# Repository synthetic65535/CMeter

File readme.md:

# CMeter
Измеритель тока фрикции.

* Используемый микроконтроллер: atmega8
* Среда разработки: KiCad
* Прошивка для микроконтроллера: [Здесь](https://github.com/synthetic65535/CMeterFirmware)

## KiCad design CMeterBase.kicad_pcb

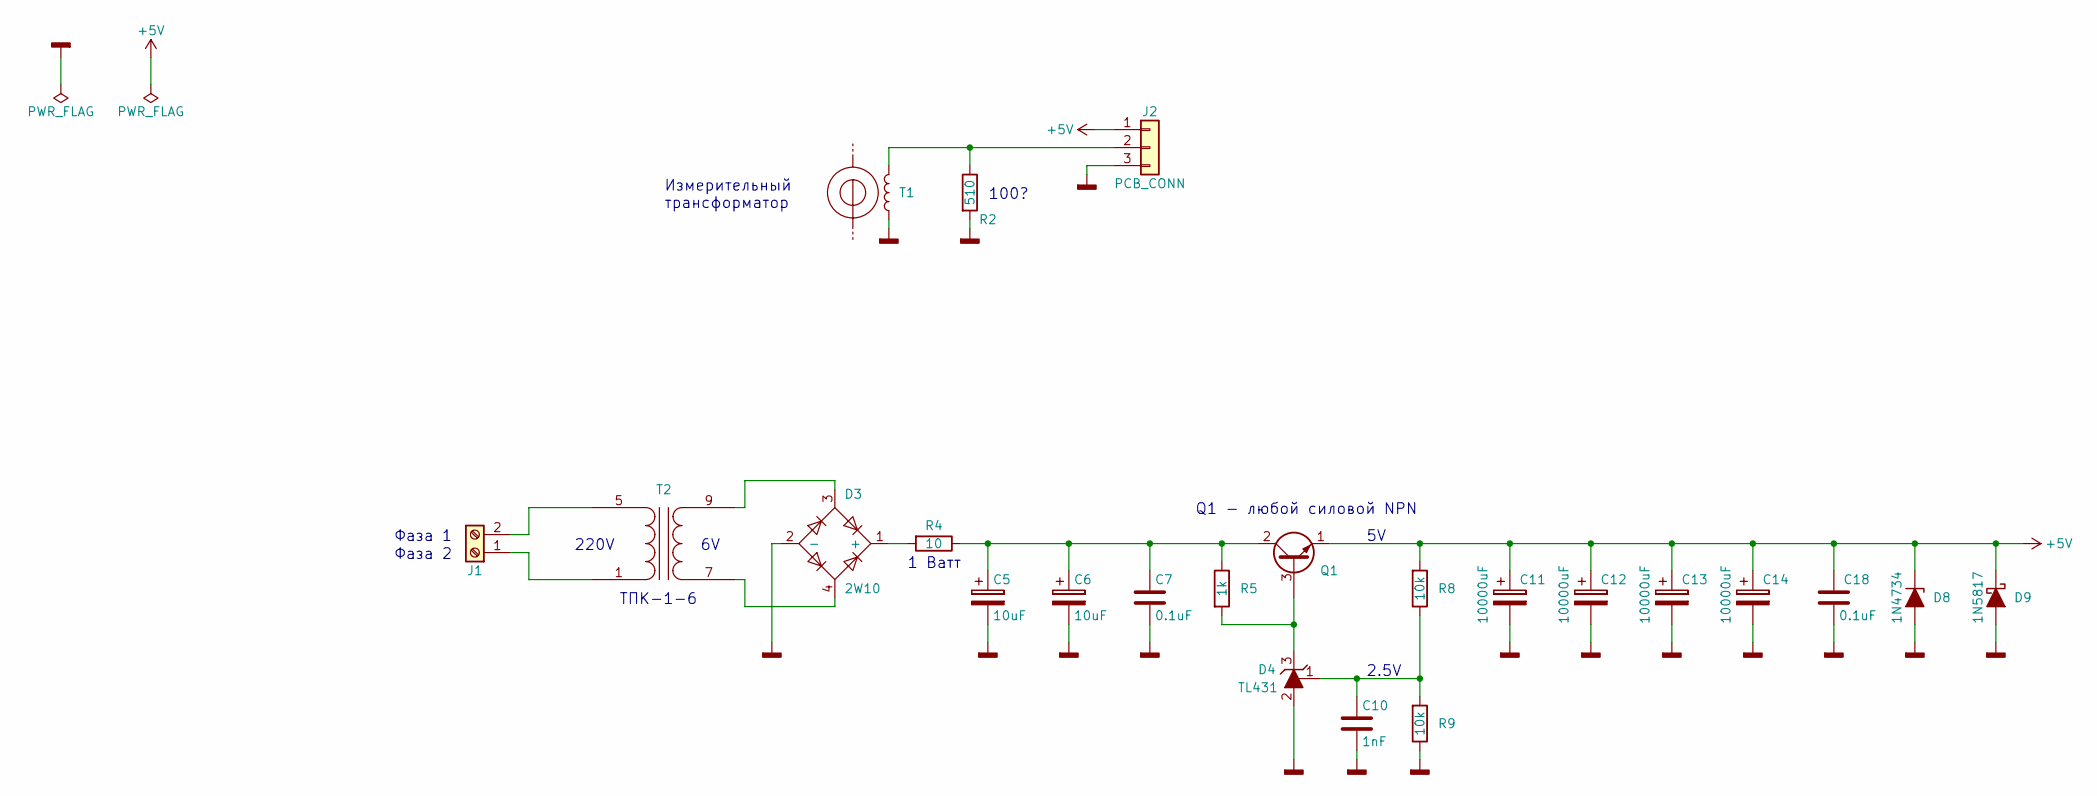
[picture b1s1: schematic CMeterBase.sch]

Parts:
C5, C6: 10uF; CP_Radial_D5.0mm_P2.00mm
C7, C18: 0.1uF; CAP
C10: 1nF; CAP
C11: 10000uF; CAP_D16_L36
C12, C13, C14: 10000uF; CAP_D16_L36-2
D3: 2W10; WOB_Bridge_Rectifier
D4: TL431
D8: 1N4734; DO-41
D9: 1N5817; DO-41
J1: Screw_Terminal_01x02; KLS2-306V-5.00-02P-2S
J2: PCB_CONN; Pin_Header_Straight_1x03_Pitch2.54mm
Q1: Q_NPN_ECB; TO-126_Horizontal
R2: 510; RES
R4: 10; RES1W
R5: 1k; RES
R8, R9: 10k; RES
T1: L_Measure; AC-1005_ZMCT102
T2: TPK-2-6; TPK-1

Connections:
+5V: C11.1, C12.1, C13.1, C14.1, C18.1, D8.1 (K), D9.1 (K), J2.1, Q1.1 (E), R8.2
GNDD: C5.2, C6.2, C7.2, C10.2, C11.2, C12.2, C13.2, C14.2, C18.2, D3.2 (-), D4.2 (A), D8.2 (A), D9.2 (A), J2.3, R2.2, R9.1, T1.1
unnamed: C5.1, C6.1, C7.1, Q1.2 (C), R4.1, R5.1
unnamed: C10.1, D4.1 (REF), R8.1, R9.2
unnamed: D3.1 (+), R4.2
unnamed: D3.3, T2.9 (SA)
unnamed: D3.4, T2.7 (SB)
unnamed: D4.3 (K), Q1.3 (B), R5.2
unnamed: J1.1, T2.1 (AA)
unnamed: J1.2, T2.5 (AB)
unnamed: J2.2, R2.1, T1.2

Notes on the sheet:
Фаза 2
Фаза 1
Измерительный трансформатор
220V
1 Ватт
2.5V
Q1 - любой силовой NPN
100?
ТПК-1-6

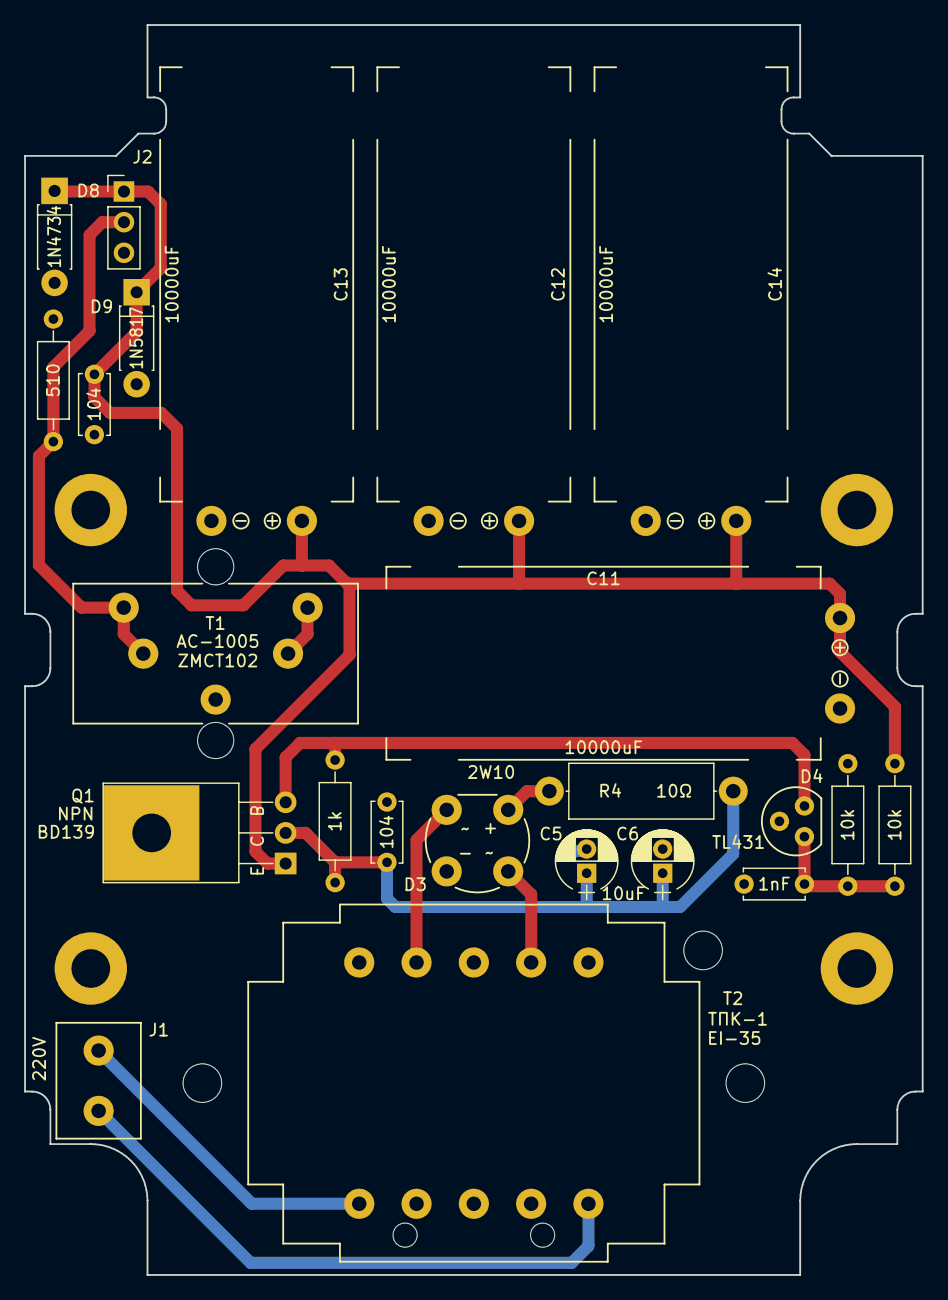
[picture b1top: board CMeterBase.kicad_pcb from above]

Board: 2 copper layers, 74.4 x 103.6 mm, 24 parts (0 on the bottom side), 11 nets.

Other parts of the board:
CASE: Case_G1202_Base; Case_G1202_Base-2

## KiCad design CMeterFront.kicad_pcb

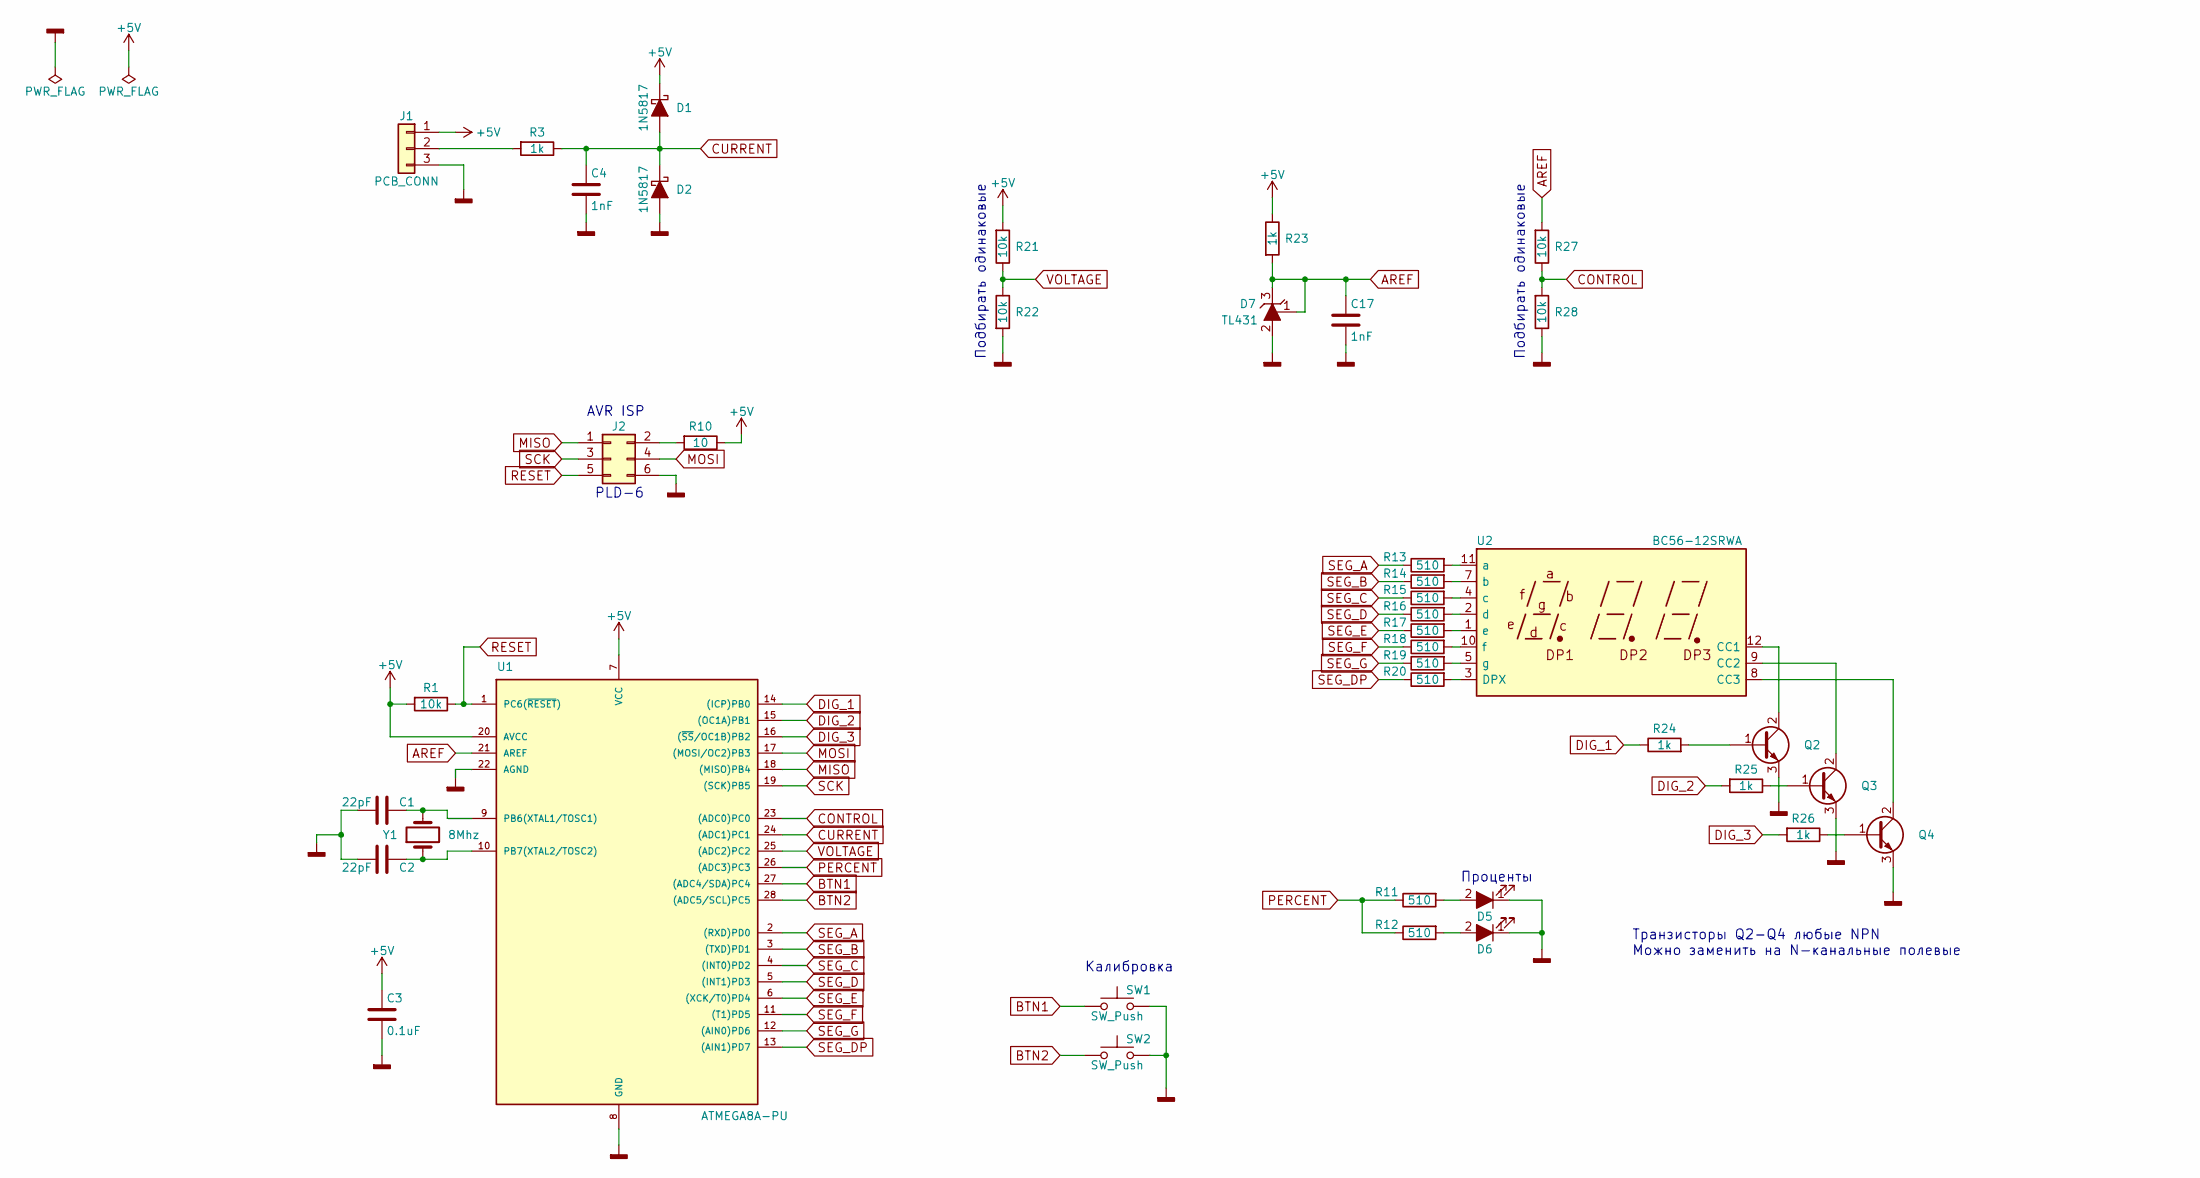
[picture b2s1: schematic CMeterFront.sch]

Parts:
C1, C2: 22pF; CAP
C3: 0.1uF; CAP
C4, C17: 1nF; CAP
D1, D2: 1N5817; DO-41
D5, D6: LED_ALT; LED_D5.0mm
D7: TL431
J1: PCB_CONN; Pin_Header_Straight_1x03_Pitch2.54mm
J2: PLD-6; AVR_ISP
Q2, Q3, Q4: Q_NPN_BCE; Q_BCE
R1, R21, R22, R27, R28: 10k; RES
R3, R23, R24, R25, R26: 1k; RES
R10: 10; RES
R11, R12, R13, R14, R15, R16, R17, R18, R19, R20: 510; RES
SW1, SW2: SW_Push; SW_PUSH_6mm_h5mm
U1: ATMEGA8A-PU; TRS-28_Connfly
U2: BC56-12SRWA; BC56-12SRWA-2
Y1: 8Mhz; Crystal_HC49-4H_Vertical

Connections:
+5V: C3.1, D1.1 (K), J1.1, R1.2, R10.1, R21.2, R23.1, U1.7 (VCC), U1.20 (AVCC)
AREF: C17.1, D7.1 (REF), D7.3 (K), R23.2, R27.2, U1.21 (AREF)
BTN1: SW1.1, U1.27 ((ADC4/SDA)PC4)
BTN2: SW2.1, U1.28 ((ADC5/SCL)PC5)
CONTROL: R27.1, R28.2, U1.23 ((ADC0)PC0)
CURRENT: C4.1, D1.2 (A), D2.1 (K), R3.1, U1.24 ((ADC1)PC1)
DIG_1: R24.1, U1.14 ((ICP)PB0)
DIG_2: R25.2, U1.15 ((OC1A)PB1)
DIG_3: R26.2, U1.16 ((~SS~/OC1B)PB2)
GNDD: C1.2, C2.2, C3.2, C4.2, C17.2, D2.2 (A), D5.1 (K), D6.1 (K), D7.2 (A), J1.3, J2.6, Q2.3 (E), Q3.3 (E), Q4.3 (E), R22.2, R28.1, SW1.2, SW2.2, U1.8 (GND), U1.22 (AGND)
MISO: J2.1, U1.18 ((MISO)PB4)
MOSI: J2.4, U1.17 ((MOSI/OC2)PB3)
unnamed: C1.1, U1.9 (PB6(XTAL1/TOSC1)), Y1.2
unnamed: C2.1, U1.10 (PB7(XTAL2/TOSC2)), Y1.1
unnamed: D5.2 (A), R11.2
unnamed: D6.2 (A), R12.2
unnamed: J1.2, R3.2
unnamed: J2.2, R10.2
unnamed: Q2.1 (B), R24.2
unnamed: Q2.2 (C), U2.12 (CC1)
unnamed: Q3.1 (B), R25.1
unnamed: Q3.2 (C), U2.9 (CC2)
unnamed: Q4.1 (B), R26.1
unnamed: Q4.2 (C), U2.8 (CC3)
unnamed: R13.2, U2.11 (a)
unnamed: R14.2, U2.7 (b)
unnamed: R15.2, U2.4 (c)
unnamed: R16.2, U2.2 (d)
unnamed: R17.2, U2.1 (e)
unnamed: R18.2, U2.10 (f)
unnamed: R19.2, U2.5 (g)
unnamed: R20.2, U2.3 (DPX)
PERCENT: R11.1, R12.1, U1.26 ((ADC3)PC3)
RESET: J2.5, R1.1, U1.1 (PC6(~RESET~))
SCK: J2.3, U1.19 ((SCK)PB5)
SEG_A: R13.1, U1.2 ((RXD)PD0)
SEG_B: R14.1, U1.3 ((TXD)PD1)
SEG_C: R15.1, U1.4 ((INT0)PD2)
SEG_D: R16.1, U1.5 ((INT1)PD3)
SEG_DP: R20.1, U1.13 ((AIN1)PD7)
SEG_E: R17.1, U1.6 ((XCK/T0)PD4)
SEG_F: R18.1, U1.11 ((T1)PD5)
SEG_G: R19.1, U1.12 ((AIN0)PD6)
VOLTAGE: R21.1, R22.1, U1.25 ((ADC2)PC2)

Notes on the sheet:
PLD-6
AVR ISP
Проценты
Транзисторы Q2-Q4 любые NPN Можно заменить на N-канальные полевые
Подбирать одинаковые
Калибровка

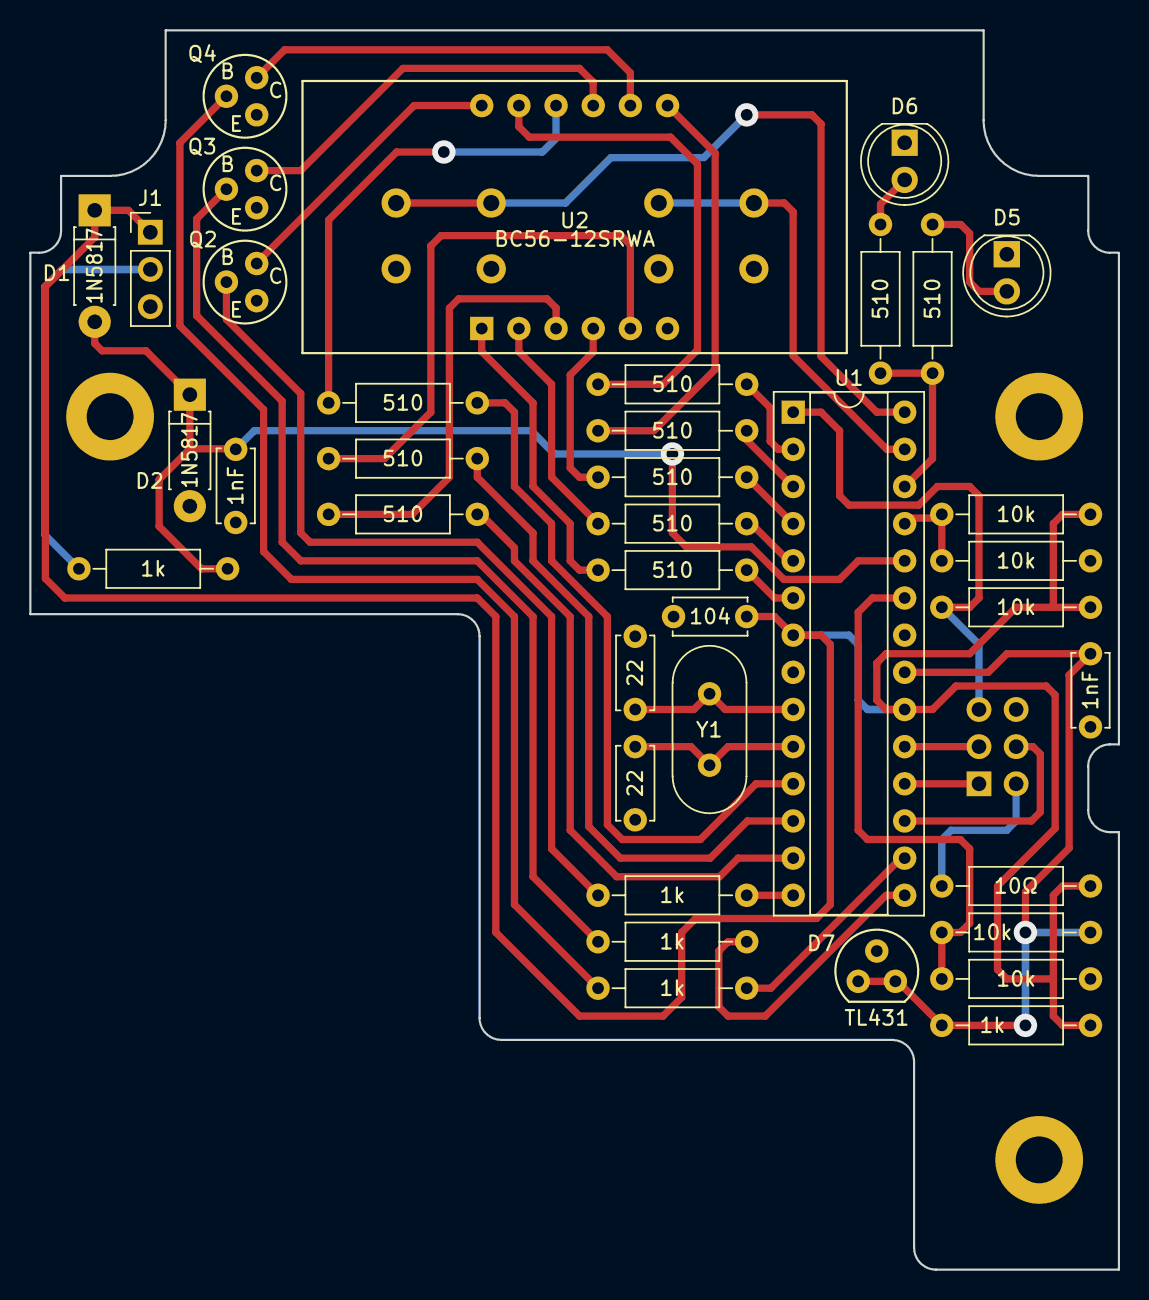
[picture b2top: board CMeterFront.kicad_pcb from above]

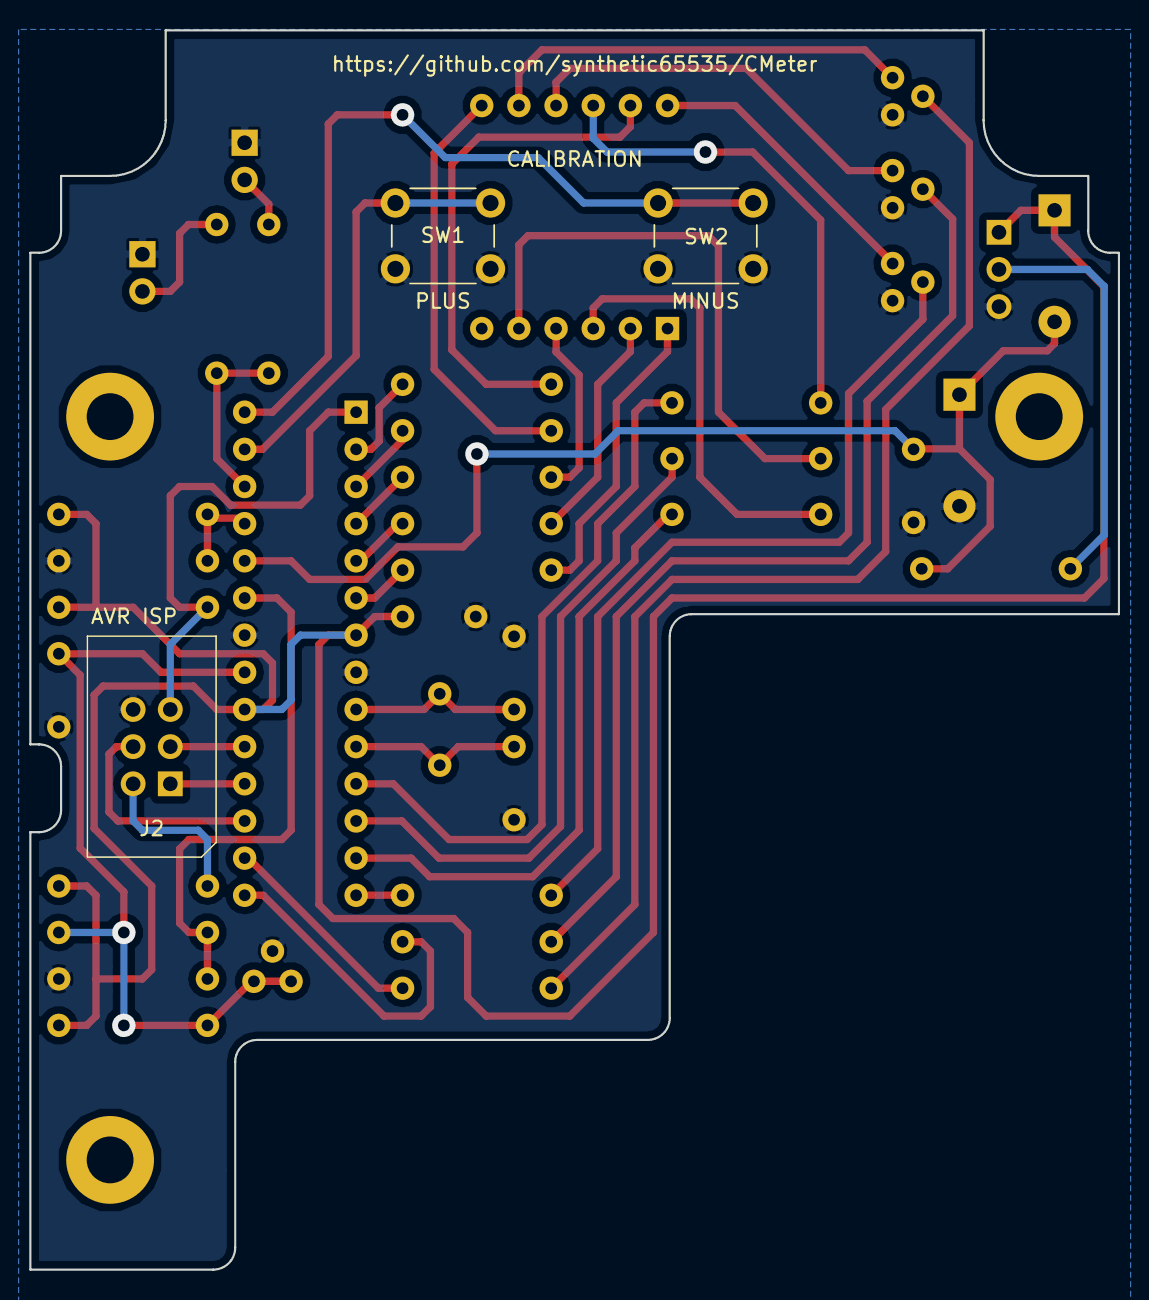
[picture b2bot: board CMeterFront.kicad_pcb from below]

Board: 2 copper layers, 74.4 x 84.7 mm, 43 parts (3 on the bottom side), 44 nets.

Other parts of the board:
CASE: Case_G1202_Front-2
T1: L_Measure; AC-1005_ZMCT102_Enclosure

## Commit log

2019-01-22 internal milling areas changed for jlcpcb
